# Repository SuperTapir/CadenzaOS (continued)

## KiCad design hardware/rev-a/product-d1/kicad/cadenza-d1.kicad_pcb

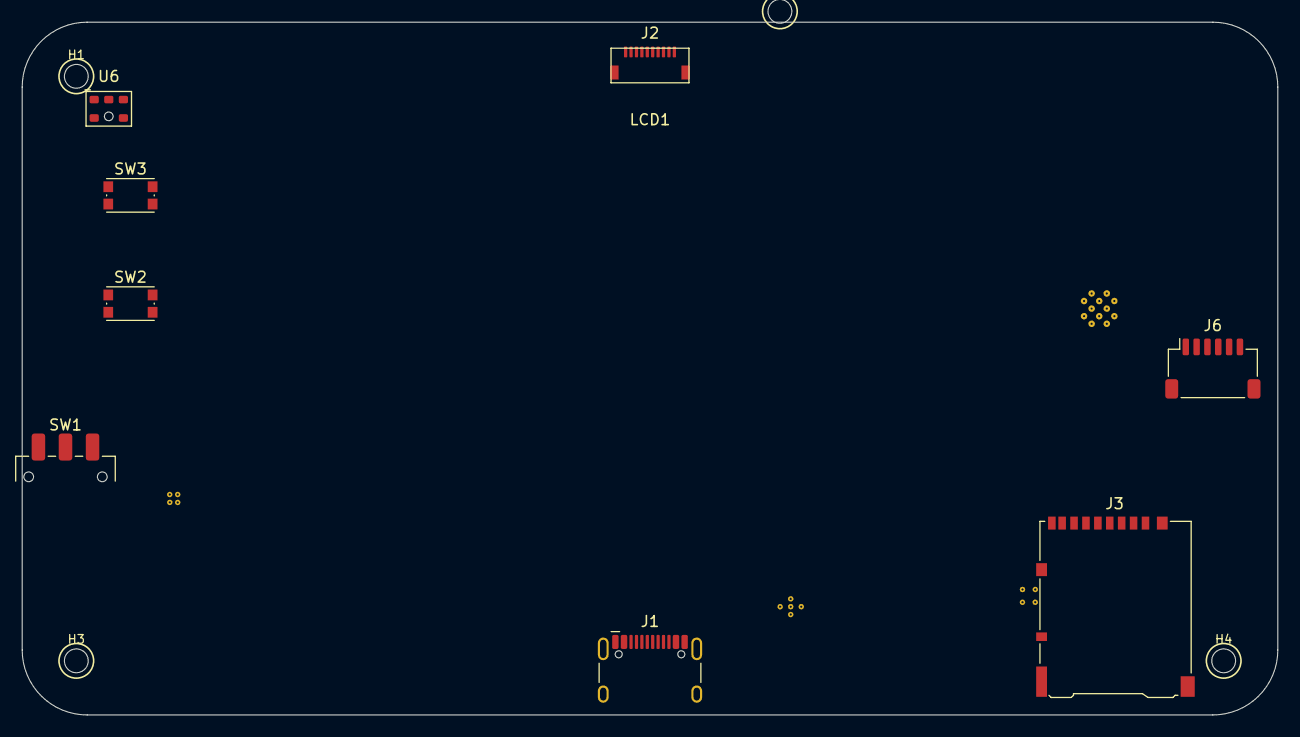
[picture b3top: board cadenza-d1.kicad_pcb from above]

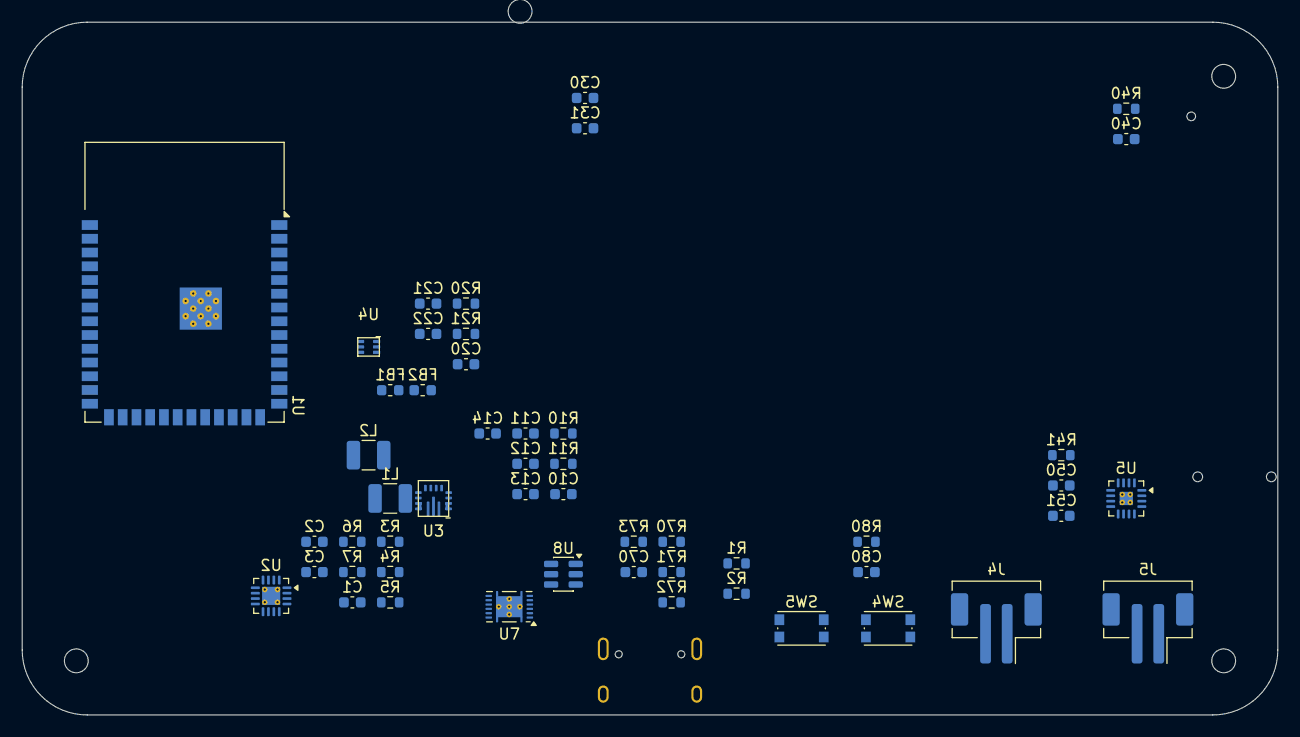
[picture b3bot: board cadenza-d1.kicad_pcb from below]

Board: 4 copper layers, 116.0 x 64.0 mm, 64 parts (51 on the bottom side), 59 nets, no tracks yet.

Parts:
C1, C2, C3, C10, C11, C20, C50: 10uF; C_0603_1608Metric
C12, C13, C21, C22: 22uF; C_0603_1608Metric
C14, C31, C40, C51: 100nF; C_0603_1608Metric
C30, C70, C80: 1uF; C_0603_1608Metric
FB1, FB2: 600R@100MHz; L_0603_1608Metric
H1: NPTH 2.2mm; H1
H2: NPTH 2.2mm; H2
H3: NPTH 2.2mm; H3
H4: NPTH 2.2mm; H4
J1: USB-C USB2 Sink; USB_C_Receptacle_HCTL_HC-TYPE-C-16P-01A
J2: LS027B7DH01 FPC; Hirose_FH34SRJ-10S-0.5SH
J3: microSD push-push; microSD_HC_Hirose_DM3AT-SF-PEJM5
J4: LiPo 1S; JST_PH_B2B-PH-SM4-TB_1x02-1MP_P2.00mm_Vertical
J5: Speaker 8R 1-2W; JST_PH_B2B-PH-SM4-TB_1x02-1MP_P2.00mm_Vertical
J6: Encoder daughterboard; JST_SH_SM06B-SRSS-TB_1x06-1MP_P1.00mm_Horizontal
L1: 1.2uH Isat>=4.5A; L_1210_3225Metric
L2: 1uH Isat>=4.5A; L_1210_3225Metric
LCD1: LS027B7DH01 62.8x42.82; Sharp_LS027B7DH01_Mechanical
R1, R2: 5.1k; R_0603_1608Metric
R3, R5: 1.5k; R_0603_1608Metric
R4: 1.18k; R_0603_1608Metric
R6: 47k; R_0603_1608Metric
R7, R72, R80: 10k; R_0603_1608Metric
R10: 470k; R_0603_1608Metric
R11: 150k; R_0603_1608Metric
R20: 732k; R_0603_1608Metric
R21, R41: 100k; R_0603_1608Metric
R40: 100R; R_0603_1608Metric
R70, R71: 4.7k; R_0603_1608Metric
R73: 0.01R 1%; R_0603_1608Metric
SW1: POWER RUN/OFF; SW_SPDT_CK_JS102011SAQN
SW2: B; SW_Push_1P1T_NO_CK_KMR2
SW3: MENU; SW_Push_1P1T_NO_CK_KMR2
SW4: RESET; SW_Push_1P1T_NO_CK_KMR2
SW5: BOOT; SW_Push_1P1T_NO_CK_KMR2
U1: ESP32-S3-WROOM-1-N16R8; ESP32-S3-WROOM-1
U2: BQ24074RGTR; VQFN-16-1EP_3x3mm_P0.5mm_EP1.68x1.68mm_ThermalVias
U3: TPS63070RNMR; TI_RNM0015A_VQFN-HR-15_TI4222000B
U4: TPS61023DRLR; TI_DRL0006A_SOT-563
U5: MAX98357AETE+T; TQFN-16-1EP_3x3mm_P0.5mm_EP1.23x1.23mm_ThermalVias
U6: IM73D122V01; Infineon_IM73D122V01_PG-LLGA-5-3
U7: BQ27441DRZR-G1A; Texas_S-PDSO-N12
U8: USBLC6-2SC6; SOT-23-6

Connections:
/+3V3_MAIN: C12.1, C13.1, C40.1, J3.4 (VDD), J6.1, R10.1, R41.2, R70.2, R71.2, R80.1, U1.2 (3V3), U2.6 (EN1), U3.1 (PS_SYNC), U3.7 (VOUT), U3.8 (VOUT), U6.2 (VDD)
/+5V_AUDIO: C50.1, C51.1, FB2.2, U5.7 (VDD), U5.8 (VDD)
/+5V_LCD: C30.1, C31.1, FB1.2, J2.6 (VDDA), J2.7 (VDD)
/+5V_MEDIA: C21.1, C22.1, FB1.1, FB2.1, R20.1, U4.6 (VOUT)
/AMP_EN: R41.1, U1.34 (GPIO41), U5.4 (SD_MODE)
/A_SW: J6.5, U1.6 (GPIO6)
/BAT_TS: R7.1, U2.1 (TS)
/BOOST_SW: L2.2, U4.5 (SW)
/BOOT_N: SW5.1 (A), U1.27 (GPIO0)
/B_SW: SW2.1 (A), U1.24 (GPIO47)
/CC1: J1.A5 (CC1), R1.1
/CC2: J1.B5 (CC2), R2.1
/CHG_N: U1.10 (GPIO17), U2.9 (CHG)
/ENC_A: J6.3, U1.4 (GPIO4)
/ENC_B: J6.4, U1.5 (GPIO5)
/ESP_EN: C80.1, R80.2, SW4.1 (A), U1.3 (EN)
/FB_3V3: R10.2, R11.1, U3.5 (FB)
/FB_5V: R20.2, R21.1, U4.1 (FB)
/GAUGE_BIN: R72.1, U7.9 (BIN)
/GAUGE_SRN: R73.2, U7.7 (SRN)
/GAUGE_SRP: R73.1, U7.11 (SRP)
/GND: C1.2, C2.2, C3.2, C10.2, C11.2, C12.2, C13.2, C14.2, C20.2, C21.2, C22.2, C30.2, C31.2, C40.2, C50.2, C51.2, C70.2, C80.2, J1.A1 (GND), J1.A12 (GND), J1.B1 (GND), J1.B12 (GND), J2.9 (VSS), J2.10 (VSSA), J3.6 (VSS), J3.10 (SHIELD), J4.2, J6.2, R1.2, R2.2, R3.2, R4.2, R5.2, R6.2, R7.2, R11.2, R21.2, R72.2, SW1.2 (B), SW2.2 (B), SW3.2 (B), SW4.2 (B), SW5.2 (B), U1.1 (GND), U1.40 (GND), U1.41 (EPAD), U2.4 (CE), U2.5 (EN2), U2.8 (VSS), U2.17 (EP), U3.4 (GND), U3.6 (FB2), U3.10 (PGND), U3.15 (VSEL), U4.4 (GND), U5.2 (GAIN_SLOT), U5.3 (GND), U5.11 (GND), U5.15 (GND), U5.17 (EP), U6.4 (LR), U6.5 (GND), U7.4 (VSS), U7.13 (EP), U8.2 (GND)
/I2C_SCL: R71.1, U1.11 (GPIO18), U7.5 (SCL)
/I2C_SDA: R70.1, U1.12 (GPIO8), U7.1 (SDA)
/I2S_BCLK: U1.16 (GPIO46), U5.16 (BCLK)
/I2S_DIN: U1.7 (GPIO7), U5.1 (DIN)
/I2S_LRCLK: U1.33 (GPIO40), U5.14 (LRCLK)
/ILIM_SET: R3.1, U2.12 (ILIM)
/ISET_SET: R4.1, U2.16 (ISET)
/ITERM_SET: R5.1, U2.15 (ITERM)
/L3V3_A: L1.1, U3.11 (L1)
/L3V3_B: L1.2, U3.9 (L2)
/LCD_DISP: J2.5 (DISP), U1.21 (GPIO13)
/LCD_EXTCOMIN: J2.4 (EXTCOMIN), U1.22 (GPIO14)
/LCD_EXTMODE: J2.8 (EXTMODE), U1.8 (GPIO15)
/LCD_SCLK: J2.1 (SCLK), U1.20 (GPIO12)
/LCD_SCS: J2.3 (SCS), U1.18 (GPIO10)
/LCD_SI: J2.2 (SI), U1.19 (GPIO11)
/MENU_SW: SW3.1 (A), U1.25 (GPIO48)
/PDM_CLK: U1.32 (GPIO39), U6.3 (CLOCK)
/PDM_DATA: R40.2, U1.35 (GPIO42)
/PDM_DATA_RAW: R40.1, U6.1 (DATA)
/RUN_EN: SW1.1 (A), U3.14 (EN), U4.2 (EN)
/SD_CLK: J3.5 (CLK), U1.29 (GPIO36)
/SD_CMD: J3.3 (CMD), U1.28 (GPIO35)
/SD_CS: J3.2 (CD_DAT3), U1.31 (GPIO38)
/SD_DAT0: J3.7 (DAT0), U1.30 (GPIO37)
/SPK+: J5.1, U5.9 (OUTP)
/SPK-: J5.2, U5.10 (OUTN)
/TMR_SET: R6.1, U2.14 (TMR)
/USB_D+: U1.14 (GPIO20), U8.4 (IO2)
/USB_D+_CONN: J1.A6 (D+), J1.B6 (D+), U8.3 (IO2)
/USB_D-: U1.13 (GPIO19), U8.6 (IO1)
/USB_D-_CONN: J1.A7 (D-), J1.B7 (D-), U8.1 (IO1)
/VAUX_3V3: C14.1, U3.3 (VAUX)
/VBAT: C3.1, J4.1, U2.2 (BAT), U2.3 (BAT)
/VBAT_SENSE: C70.1, U7.6 (BAT)
/VBUS: C1.1, J1.A4 (VBUS), J1.A9 (VBUS), J1.B4 (VBUS), J1.B9 (VBUS), U2.13 (IN), U8.5 (VBUS)
/VSYS: C2.1, C10.1, C11.1, C20.1, L2.1, U2.10 (OUT), U2.11 (OUT), U3.12 (VIN), U3.13 (VIN), U4.3 (VIN)

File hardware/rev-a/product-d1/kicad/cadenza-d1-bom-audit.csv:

"Refs","Value","Footprint","Qty","DNP"
"C1","10uF","Capacitor_SMD:C_0603_1608Metric","1",""
"C2","10uF","Capacitor_SMD:C_0603_1608Metric","1",""
"C3","10uF","Capacitor_SMD:C_0603_1608Metric","1",""
"C10","10uF","Capacitor_SMD:C_0603_1608Metric","1",""
"C11","10uF","Capacitor_SMD:C_0603_1608Metric","1",""
"C12","22uF","Capacitor_SMD:C_0603_1608Metric","1",""
"C13","22uF","Capacitor_SMD:C_0603_1608Metric","1",""
"C14","100nF","Capacitor_SMD:C_0603_1608Metric","1",""
"C20","10uF","Capacitor_SMD:C_0603_1608Metric","1",""
"C21","22uF","Capacitor_SMD:C_0603_1608Metric","1",""
"C22","22uF","Capacitor_SMD:C_0603_1608Metric","1",""
"C30","1uF","Capacitor_SMD:C_0603_1608Metric","1",""
"C31","100nF","Capacitor_SMD:C_0603_1608Metric","1",""
"C40","100nF","Capacitor_SMD:C_0603_1608Metric","1",""
"C50","10uF","Capacitor_SMD:C_0603_1608Metric","1",""
"C51","100nF","Capacitor_SMD:C_0603_1608Metric","1",""
"C70","1uF","Capacitor_SMD:C_0603_1608Metric","1",""
"C80","1uF","Capacitor_SMD:C_0603_1608Metric","1",""
"FB1","600R@100MHz","Inductor_SMD:L_0603_1608Metric","1",""
"FB2","600R@100MHz","Inductor_SMD:L_0603_1608Metric","1",""
"J1","USB-C USB2 Sink","Connector_USB:USB_C_Receptacle_HCTL_HC-TYPE-C-16P-01A","1",""
"J2","LS027B7DH01 FPC","Cadenza_D1:Hirose_FH34SRJ-10S-0.5SH","1",""
"J3","microSD push-push","Connector_Card:microSD_HC_Hirose_DM3AT-SF-PEJM5","1",""
"J4","LiPo 1S","Connector_JST:JST_PH_B2B-PH-SM4-TB_1x02-1MP_P2.00mm_Vertical","1",""
"J5","Speaker 8R 1-2W","Connector_JST:JST_PH_B2B-PH-SM4-TB_1x02-1MP_P2.00mm_Vertical","1",""
"J6","Encoder daughterboard","Connector_JST:JST_SH_SM06B-SRSS-TB_1x06-1MP_P1.00mm_Horizontal","1",""
"L1","1.2uH Isat>=4.5A","Inductor_SMD:L_1210_3225Metric","1",""
"L2","1uH Isat>=4.5A","Inductor_SMD:L_1210_3225Metric","1",""
"R1","5.1k","Resistor_SMD:R_0603_1608Metric","1",""
"R2","5.1k","Resistor_SMD:R_0603_1608Metric","1",""
"R3","1.5k","Resistor_SMD:R_0603_1608Metric","1",""
"R4","1.18k","Resistor_SMD:R_0603_1608Metric","1",""
"R5","1.5k","Resistor_SMD:R_0603_1608Metric","1",""
"R6","47k","Resistor_SMD:R_0603_1608Metric","1",""
"R7","10k","Resistor_SMD:R_0603_1608Metric","1",""
"R10","470k","Resistor_SMD:R_0603_1608Metric","1",""
"R11","150k","Resistor_SMD:R_0603_1608Metric","1",""
"R20","732k","Resistor_SMD:R_0603_1608Metric","1",""
"R21","100k","Resistor_SMD:R_0603_1608Metric","1",""
"R40","100R","Resistor_SMD:R_0603_1608Metric","1",""
"R41","100k","Resistor_SMD:R_0603_1608Metric","1",""
"R70","4.7k","Resistor_SMD:R_0603_1608Metric","1",""
"R71","4.7k","Resistor_SMD:R_0603_1608Metric","1",""
"R72","10k","Resistor_SMD:R_0603_1608Metric","1",""
"R73","0.01R 1%","Resistor_SMD:R_0603_1608Metric","1",""
"R80","10k","Resistor_SMD:R_0603_1608Metric","1",""
"SW1","POWER RUN/OFF","Button_Switch_SMD:SW_SPDT_CK_JS102011SAQN","1",""
"SW2","B","Button_Switch_SMD:SW_Push_1P1T_NO_CK_KMR2","1",""
"SW3","MENU","Button_Switch_SMD:SW_Push_1P1T_NO_CK_KMR2","1",""
"SW4","RESET","Button_Switch_SMD:SW_Push_1P1T_NO_CK_KMR2","1",""
"SW5","BOOT","Button_Switch_SMD:SW_Push_1P1T_NO_CK_KMR2","1",""
"U1","ESP32-S3-WROOM-1-N16R8","RF_Module:ESP32-S3-WROOM-1","1",""
"U2","BQ24074RGTR","Package_DFN_QFN:VQFN-16-1EP_3x3mm_P0.5mm_EP1.68x1.68mm_ThermalVias","1",""
"U3","TPS63070RNMR","Cadenza_D1:TI_RNM0015A_VQFN-HR-15_TI4222000B","1",""
"U4","TPS61023DRLR","Cadenza_D1:TI_DRL0006A_SOT-563","1",""
"U5","MAX98357AETE+T","Package_DFN_QFN:TQFN-16-1EP_3x3mm_P0.5mm_EP1.23x1.23mm_ThermalVias","1",""
"U6","IM73D122V01","Cadenza_D1:Infineon_IM73D122V01_PG-LLGA-5-3","1",""
"U7","BQ27441DRZR-G1A","Package_SON:Texas_S-PDSO-N12","1",""
"U8","USBLC6-2SC6","Package_TO_SOT_SMD:SOT-23-6","1",""

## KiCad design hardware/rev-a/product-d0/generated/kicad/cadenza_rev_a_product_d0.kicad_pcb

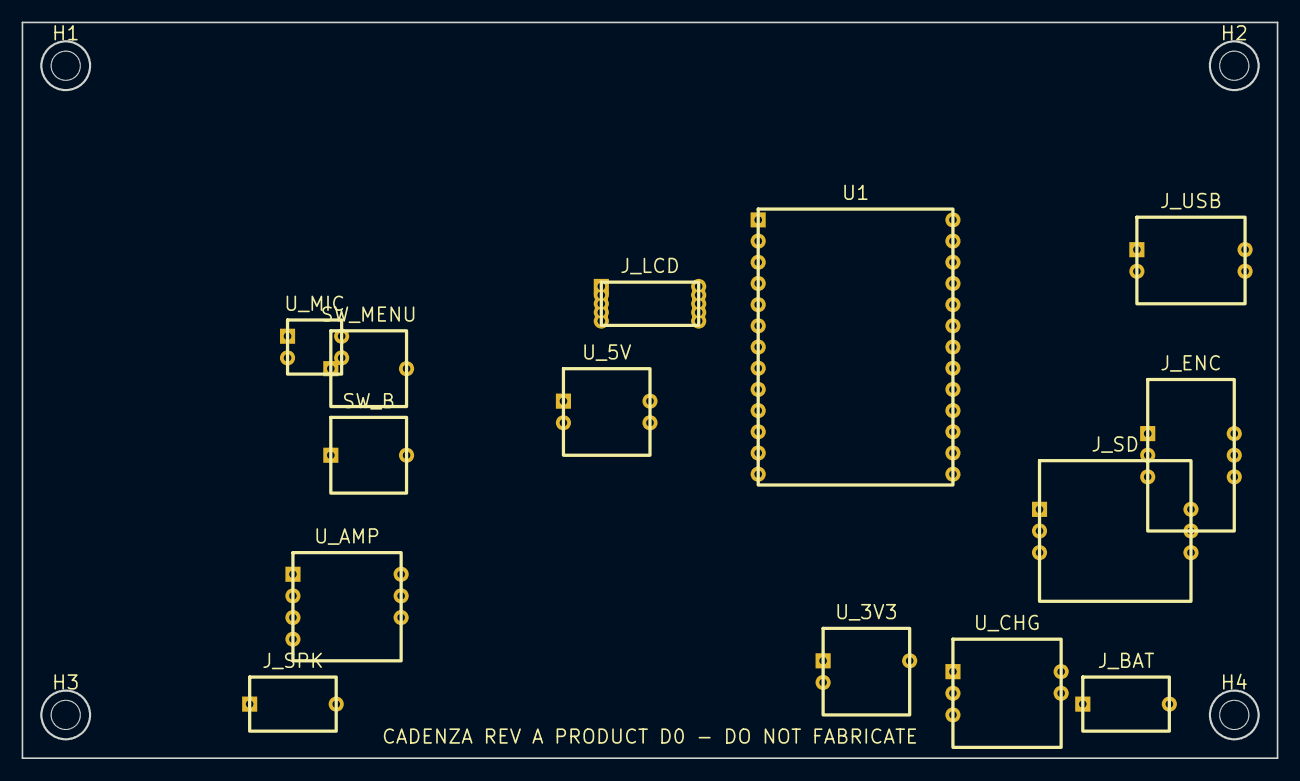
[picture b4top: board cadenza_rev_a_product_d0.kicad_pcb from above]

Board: 4 copper layers, 116.0 x 68.0 mm, 18 parts (0 on the bottom side), 31 nets, no tracks yet.

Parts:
H1, H2, H3, H4: MountingHole
J_BAT: JST-PH-2; J_BAT
J_ENC: ENCODER_DB_1x6; J_ENC
J_LCD: FH34SRJ-10S-0.5SH; J_LCD
J_SD: MICROSD; J_SD
J_SPK: JST-PH-2; J_SPK
J_USB: USB-C-USB2; J_USB
SW_B: TACT_B; SW_B
SW_MENU: TACT_MENU; SW_MENU
U1: ESP32-S3-WROOM-1-N16R8; U1
U_3V3: AP2112K-3.3; U_3V3
U_5V: TPS61023; U_5V
U_AMP: MAX98357A; U_AMP
U_CHG: BQ24074; U_CHG
U_MIC: IM69D130; U_MIC

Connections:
+3V3: J_ENC.1, J_ENC.6, J_SD.1, U1.2, U_3V3.3, U_MIC.1
+5V_LCD: J_LCD.6, J_LCD.7, U_5V.4, U_AMP.1
A_SW: J_ENC.5, U1.13
B_SW: SW_B.1, U1.14
ENC_A: J_ENC.3, U1.11
ENC_B: J_ENC.4, U1.12
GND: J_BAT.2, J_ENC.2, J_LCD.8, J_LCD.9, J_LCD.10, J_SD.2, J_USB.2, SW_B.2, SW_MENU.2, U1.1, U_3V3.2, U_5V.2, U_AMP.2, U_CHG.2, U_MIC.2
I2C_SCL: U1.26, U_CHG.5
I2C_SDA: U1.25, U_CHG.4
LCD_5V_EN: U1.10, U_5V.3
LCD_DISP: J_LCD.5, U1.9
LCD_EXTCOMIN: J_LCD.4, U1.8
LCD_SCLK: J_LCD.1, U1.5
LCD_SCS: J_LCD.3, U1.7
LCD_SI: J_LCD.2, U1.6
MENU_SW: SW_MENU.1, U1.15
MIC_CLK: U1.16, U_MIC.3
MIC_DATA: U1.17, U_MIC.4
SD_CS: J_SD.6, U1.24
SD_MISO: J_SD.5, U1.23
SD_MOSI: J_SD.4, U1.22
SD_SCK: J_SD.3, U1.21
SPK+: J_SPK.1, U_AMP.6
SPK-: J_SPK.2, U_AMP.7
SPK_BCLK: U1.18, U_AMP.3
SPK_DIN: U1.20, U_AMP.5
SPK_LRCLK: U1.19, U_AMP.4
USB_D+: J_USB.4, U1.4
USB_D-: J_USB.3, U1.3
VBAT: J_BAT.1, U_3V3.1, U_5V.1, U_CHG.3
VBUS: J_USB.1, U_CHG.1

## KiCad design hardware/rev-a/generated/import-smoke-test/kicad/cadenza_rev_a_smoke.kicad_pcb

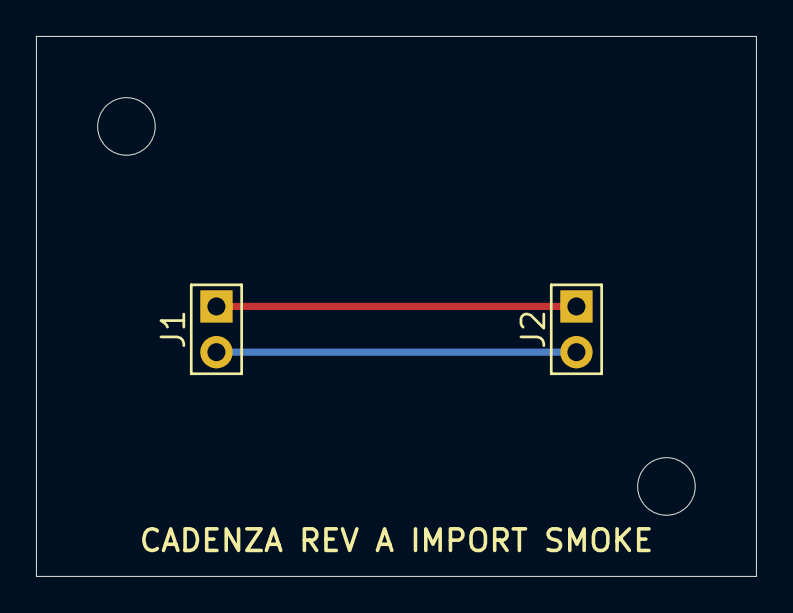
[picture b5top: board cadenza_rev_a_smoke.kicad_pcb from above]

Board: 4 copper layers, 40.0 x 30.0 mm, 4 parts (0 on the bottom side), 2 nets.

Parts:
H1, H2: MOUNTING_HOLE; MountingHole_3.2mm
J1: SMOKE_IN; Conn_01x02
J2: SMOKE_OUT; Conn_01x02

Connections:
GND: J1.2, J2.2
TEST_SIG: J1.1, J2.1

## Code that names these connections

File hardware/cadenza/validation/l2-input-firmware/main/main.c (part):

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#define CONFIG_L2_EVENT_LOGGING 0
#endif

#define GPIO_ENC_A GPIO_NUM_15
#define GPIO_ENC_B GPIO_NUM_16
#define GPIO_BUTTON_A GPIO_NUM_17
#define GPIO_BUTTON_B GPIO_NUM_5
#define GPIO_BUTTON_MENU GPIO_NUM_8
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
static inline uint8_t encoder_state(void)
{
    return (uint8_t)((input_pressed(GPIO_ENC_A) ? 1U : 0U) << 1) |
           (uint8_t)(input_pressed(GPIO_ENC_B) ? 1U : 0U);
}

static void encoder_gpio_isr(void *argument)
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    const BaseType_t queued = xQueueSendFromISR(s_encoder_queue, &edge, &task_woken);

    portENTER_CRITICAL_ISR(&s_isr_stats_lock);
    if (source == GPIO_ENC_A) {
        s_encoder_a_edges++;
    } else {
        s_encoder_b_edges++;
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
static void print_status_locked(void)
{
    const bool raw_a = input_pressed(GPIO_ENC_A);
    const bool raw_b = input_pressed(GPIO_ENC_B);
    uint32_t encoder_a_edges;
    uint32_t encoder_b_edges;
    uint32_t encoder_queue_overflows;
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
void app_main(void)
{
    const uint64_t input_mask = (1ULL << GPIO_ENC_A) | (1ULL << GPIO_ENC_B) |
                                (1ULL << GPIO_BUTTON_A) | (1ULL << GPIO_BUTTON_B) |
                                (1ULL << GPIO_BUTTON_MENU);
    const gpio_config_t input_gpio_config = {
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    }

    ESP_ERROR_CHECK(gpio_install_isr_service(0));
    ESP_ERROR_CHECK(gpio_set_intr_type(GPIO_ENC_A, GPIO_INTR_ANYEDGE));
    ESP_ERROR_CHECK(gpio_set_intr_type(GPIO_ENC_B, GPIO_INTR_ANYEDGE));
    ESP_ERROR_CHECK(gpio_isr_handler_add(GPIO_ENC_A, encoder_gpio_isr,
                                         (void *)(intptr_t)GPIO_ENC_A));
    ESP_ERROR_CHECK(gpio_isr_handler_add(GPIO_ENC_B, encoder_gpio_isr,
                                         (void *)(intptr_t)GPIO_ENC_B));

    printf("\nCadenza L2 input validation only; active-low; external 10k pull-ups assumed.\n");
    printf("ENC_A=GPIO15 ENC_B=GPIO16 A(center)=GPIO17 B=GPIO5 Menu=GPIO8\n");
    printf("debounce=%dms long=%dms reverse=%u counts_per_detent=%u events=%u\n",
           CONFIG_L2_BUTTON_DEBOUNCE_MS, CONFIG_L2_BUTTON_LONG_PRESS_MS,
           s_reverse, s_counts_per_detent, s_event_logging);
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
